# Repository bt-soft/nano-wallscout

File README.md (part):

# Pulzusindukciós (PI) betonvas-kereső – Arduino Nano + DD tekercs + MCP6004 + IRLZ44N + SSD1306

> [!NOTE]
> A projekt egy kézi impulzusindukciós (PI) elven működő - **mélységbecsléssel ellátott** - betonvas-kereső, amely két D alakú tekerccsel (DD elrendezés) működik. 
>
> Platform: **Arduino Nano (ATmega328P)**.

| Jellemző | Érték |
|---|---|
| Érzékelési mélység* | ≈5–6 cm, 8 cm becsült határeset (Ø8–12 mm betonvas, a tekercsek méretétől függően) |
| Kijelzés | SSD1306 OLED (oszlop, számérték, becsült mélység), hangjelzés |
| Tápellátás | 2S vagy 3S 18650 akkumulátor a Nano VIN bemenetén (lásd: Beüzemelés) |

 *Az értékek a tesztelési körülményektől, a tekercs geometriájától és a beállításoktól függnek.

## Az impulzusindukció működési elve
A kereső két tekercset használ: egy **adó (TX)** és egy **vevő (RX)** tekercset. A [tekercsek D alakúak](https://abl.gtu.edu.tr/dosya/102/~saksoy/Metal%20Detectors/1%20GENERAL%20OVERVIEW/2%20OPERATIONAL%20PRINCIPLES/2.1%20ANTENNAS.pdf), és az egyenes oldalaikkal részben egymásra vannak csúsztatva (DD elrendezés). Az alábbiak a működés fizikai alapjait foglalják össze.

### Az adóimpulzus és a mágneses tér
A Q2 kapcsolótranzisztor bekapcsolásakor az Ltx1 adótekercsre a tápfeszültség kerül, és az árama az induktivitás miatt lineárisan nő: `I ≈ U · t / L`. 12 V-nál, 60 µs-os impulzusnál és 1 mH-s tekercsnél ez elméletileg kb. 0,7 A; a tekercs ellenállása miatt a valós csúcsáram kb. 0,6 A. Az áram körül mágneses tér épül fel, amelynek energiája `E = ½ · L · I²`.

### Kikapcsolás és örvényáramok
A Q2 lezárásakor a mágneses tér gyorsan összeomlik. Ez a tekercsben nagy feszültségtüskét (flyback) okoz, amelyet a D2 és D3 diódák korlátoznak. A gyorsan változó tér a közelében lévő fémtárgyban **örvényáramot** indukál. Az örvényáram saját mágneses teret hoz létre, amely lecsengés közben visszahat a tekercsekre.

- Az örvényáram lecsengésének időállandója függ a tárgy méretétől, vezetőképességétől és mágneses permeabilitásától. A nagyobb, jobban vezető tárgynál a lecsengés hosszabb.
- A tárgy nélküli (levegős) esetben a tekercs saját tranziense gyorsan lecseng, ezért a rövid idő múlva mért jel gyakorlatilag nulla.
- A tárgy jelenléte így a lecsengés „farkában” mérhető többletjelként jelenik meg.

### A DD elrendezés és a közvetlen áthallás kioltása
Az [adó mágneses terének](doc/Fémkereső%20tekercsek%20betonvas%20kereséshez.png) közvetlenül az RX-be jutó része sokszorosan nagyobb lenne a fém jelénél. A két D alakú tekercs átfedésénél azonban a vevőtekercs két felét az adótér ellentétes irányban metszi, ezért a **kölcsönös induktivitás (M) a megfelelő átfedésnél nullára csökken**. A pontos átfedés a beállítási eljárás (DD beállító mód) feladata. A nullpont két oldalán M előjele ellentétes, ezért a beállításkor az előjelváltást kell keresni.

Ennek eredményeként fém jelenléte nélkül az RX tekercsre elsősorban a **maradék mágneses áthallás** és a **zaj** jut. Fém jelenlétében a benne indukálódó örvényáramok mágneses tere megváltoztatja a vevőtekercsben mérhető jelet. A megfelelően beállított DD-tekercspár esetén a fém nélküli alapjel alacsony, így a céltárgy által okozott jelváltozás jól érzékelhető.

A nagyobb tekercs megfelelő kialakítás esetén növelheti az érzékelési mélységet, de az elérhető eredmény a tekercsek geometriájától, induktivitásától, ellenállásától, a meghajtóáramtól és a vevő érzékenységétől is függ. A nagyobb tekercs térben kiterjedtebb érzékelési mezőt hozhat létre, ami ugyan növelheti a hatótávolságot, ugyanakkor ronthatja a céltárgy pontos helyének behatárolását.

A projektben alkalmazott, a kisebb 6 × 5 cm-es D alakú tekercspárral az érzékelési mélység körülbelül 5-6 cm. Ez az érték kísérletileg meghatározott (fémcsipeszt közelítve a tekercsek felé), illetve a mérési körülményektől és a céltárgy jellemzőitől függ.

### Jelfeldolgozás
Az Rx jele a mérendő tárgy hatására csak kis amplitúdójú, ezért az MCP6004 két, nem invertáló fokozata (kb. 11 × 11 = 121-szeres erősítés) erősíti, majd az U2D puffer az A0 bemenetre vezeti. A jelszint a Vmid (≈ 2,5 V) körül van, így a jel pozitív és negatív irányban is mérhető.

A mérés **mintavételes**, impulzusonként két ponton:
- **S1**: a kikapcsolás után 60 µs-mal. Ekkor a tárgy örvényárama még jelen van.
- **S2**: a kikapcsolás után 600 µs-mal. Ekkor az örvényáram lecsengett, így ez az alapvonal (offset, drift).

A **jel = S1 − S2**. A különbségképzés kiejti az egyenfeszültségű eltérést és a lassú driftet. 100 impulzus átlagolása a véletlenszerű zajt csökkenti (a zaj nagyjából az átlagolt minták számának négyzetgyökével csökken). A nullázáskor mért, fém nélküli értéket a firmware kivonja, így a megjelenített érték a tárgy hatását mutatja.

### Mélységbecslés
Kis, a tekercstől távoli tárgy esetén az örvényáram jele nagyjából a távolság harmadik hatványával csökken (dipól közelítés): `S ≈ K / d³`. A `K` értéket a kalibrálás határozza meg egy ismert (5 cm) távolságban, innen `d = ∛(K / S)`. Ez a modell a tárgy méretétől és anyagától függ, ezért a kapott érték becslés, nem pontos mérés.

### A fém típusa
Az impulzus utáni jel lecsengésének időbeli jellemzői elvileg információt hordozhatnak a céltárgy anyagáról. A jelenlegi, két időpontban történő mintavételezés és a hozzá tartozó jelfeldolgozás azonban nem biztosít megbízható anyagazonosítást, ezért ezt a funkciót eltávolítottam a firmware-ből.

## Működési ciklus

1. Az IRLZ44N (Q2) 60 µs-ra bekapcsol, a **Tx tekercs** (Ltx1) árama nő.
2. Kikapcsoláskor a flyback-tüskét a D2 (UF4007) és a D3 (ZPY36, 1 W) korlátozza; a névleges **lecsípési szint** nagyjából 37 V.
3. A tranziens lecsengését az Ltx1-gyel párhuzamos R15 + R16 ág (1 kΩ fix ellenállás + 4,7 kΩ-os trimmer) csillapítja. A fémben indukált örvényáram lassabban cseng le; ez a mérendő „farok”.
4. A **külön Rx tekercs** (Lrx1) az Ltx1-gyel DD elrendezésben (részben egymásra csúsztatva) helyezkedik el, így a közvetlen áthallás közel nulla, és az erősítőbe csak a fém által keltett jel jut.
5. A Nano 1 kHz-en ismétel, és impulzusonként két ponton mintavételez az ADC-vel: **S1** a kikapcsolás után 60 µs-mal, **S2** (alapvonal) 600 µs-mal.
6. Jel = S1 − S2, 100 impulzusra átlagolva (kb. 7 Hz kijelzőfrissítés). Ez kiejti az offsetet és a lassú driftet.
7. Indításkor automatikus nullázás történik (a kereső legyen levegőben). Az alapvonal lassan követi a driftet. Egy találat előjelét a firmware megtartja; az ellenkező előjelű kilengést csak 1 másodpercnyi küszöb alatti jel után kezdi új találatként kezelni. Ha a jel kb. 3 másodpercnél tovább állandó marad (pl. nullpont-eltolódás), a firmware lassan újranulláz; egy mozdulatlanul tartott fém így néhány másodperc után elhalkul.
8. A kijelző oszlopot, számértéket és (kalibrálás után) becsült mélységet mutat. A hangjelzés magassága a jellel nő.

### Szoftverműködés – bevezető

A firmware az időkritikus részeken az **AVR hardverregisztereket közvetlenül kezeli** (`PORTD`, `PIND`, `DDRD`, `TCNT1`, `TCCR1/2`, `ADCSRA`, `ADMUX`, `PCMSK2` stb.) az Arduino `digitalWrite`/`analogRead`-jellegű, lassabb és nagyobb kódú burkolófüggvényei helyett. Ez minimalizálja a kód méretét (a program a Nano 30 KB-os flash-ébe fér), és tartja a futási sebességet: a 60 µs-os adóimpulzus, a kikapcsolás utáni S1/S2 mintavétel (0,5 µs-os Timer1-időalap, gyors, 1 MHz-es ADC-órajel) és a hangjelző (Timer2 hardveres kimenet, CPU-terhelés nélkül) így determinisztikus időzítéssel fut.

### Alvó mód (energiatakarékosság)

Ha **5 percig** nincs aktivitás, a műszer a lehető legkisebb fogyasztású **Power-down** módba kapcsol. Aktivitásnak számít: gombnyomás, aktív találat, vagy a nullázás utáni zajküszöböt meghaladó jelváltozás (a zaj nem tartja ébren). Az időkorlát a `config.h` `IDLE_SLEEP_MS` értéke.

Alvás előtt a firmware kikapcsolja a hangjelzőt, az adókaput (az adó nem kap impulzust), az OLED-et (power save, I²C leállítva), az ADC-t és az analóg bemenetek digitális pufferét, a Brown-out detektort és a watchdogot, valamint az összes perifériát (`power_all_disable`).

Ébresztés: a **kalibráló vagy a nullázó gomb** megnyomásával (pin change megszakítás), illetve a tápfeszültség újrakapcsolásával. Ébredés után a készülék újrainicializálódik, megvárja a gomb felengedését (az ébresztő nyomás nem lesz parancs), majd az indításhoz hasonlóan újranulláz – ilyenkor a kereső legyen levegőben.

Megjegyzés: a vevő (erősítő) tápját a firmware nem tudja kapcsolni, mert nincs rá vezérlőláb; az adó viszont impulzus nélkül áramot nem vesz fel. A legkisebb alvóáramhoz a vevő és a kijelző tápja hardveresen is leválasztható egy későbbi fejlesztésben.

### Gombok

Mindkét gomb a D-lábat földre húzza (belső felhúzással). A gombokat a mérés közben is figyeli a firmware, de a művelet a következő kijelzőfrissítéskor (kb. 0,1–0,2 s) hajtódik végre.

**Arduino D5 – NULLÁZÁS / beállító mód**

| Művelet | Normál (kereső) módban | DD beállító módban |
|---|---|---|
| Rövid nyomás (< 1 s), **felengedéskor** lép életbe | Újranullázás: a kijelzőn `Nullazas - legben!`, kb. 15 mérésen át (≈ 2 s) átlagolja a nullpontot és a zajszintet (a küszöb a zajhoz igazodik). Közben a kereső legyen levegőben, és ne legyen jelzés/csipogás. | Kilép a beállító módból, és újranulláz. |
| Hosszú nyomás (≥ 1 s), **még nyomva tartva** lép életbe | Belép a DD beállító módba (a `min` törlődik). | Nincs külön szerepe: a felengedéskor ugyanúgy kilép és újranulláz, mint a rövid nyomás. |

A mód váltását rövid (150 ms-os), 3 kHz-es csipogás jelzi. A hosszú nyomás után a gomb felengedése már nem indít újabb műveletet.

**Arduino D4 – KALIBRÁLÁS / KÖZÉPKERESŐ / `min` törlése**

Normál kereső módban a D4 rövid megnyomásai a következő nézetek között léptetnek: normál keresés → élő `CENTER SCAN` → `Jel-Ido` grafikon → normál keresés. A grafikon folyamatosan gyűjti a méréseket: az amplitúdó jobbról érkezik, a korábbi minták balra gördülnek, így a jel erősségének időbeli alakulása követhető. A grafikon a nullázott jel abszolút értékét mutatja; a szaggatott vízszintes vonal az adaptív küszöb. A hosszú nyomás a távolságtanító képernyőt nyitja meg (lásd lent). DD beállító módban a D4 megnyomása törli a `min` értéket (eddigi legkisebb abszolút áthallás), és újra a következő mérésből indul.

Középkereső módban a kijelző az előjeles, nullázott jelet, annak rövid gördülő grafikonját, a zajküszöböt, az első és a visszapásztázás során mért csúcsot mutatja. A firmware legalább két küszöb feletti mintával jelöltet keres, több csökkenő minta alapján becsül csúcsot, majd visszapásztázás után a két csúcserősséget hasonlítja össze. A `CSUCS MEGEROSITVE` csak ezt a jelerősség-egyezést jelenti: a mintasorszám nem pozíció, így a mód nem mér és nem jelöl ki pontos fizikai középvonalat. A visszapásztázás irányát nem nevezi meg.

A mód bekapcsolásakor a mérő legyen levegőben és fémtől távol. Ha a `ZAJOS MERES` felirat látszik, válassz kevésbé zajos helyet és nullázz újra a D5 rövid megnyomásával. Középkereső módban a driftkövetés és az automatikus újranullázás szünetel, így a hosszan a tekercs alatt tartott tárgyat nem nyomja el a háttérkövetés. A visszalépéshez nyomd meg röviden újra a D4-et.

Normál módban:

1. Tartsd lenyomva a D4-et **1 másodpercig**: megnyílik a `TANITAS 5cm` képernyő, amely folyamatosan mutatja a vett jelet, egy oszlopot és (érvényes kalibráció esetén) a becsült távolságot. A képernyőn a driftkövetés szünetel.
2. Tarts egy vasat (a használt vastípust) pontosan **5 cm**-re a tekercstől, és nyomd meg röviden a D4-et. Ha a jel a küszöb fölött van, a firmware eltárolja a `K = jel · 5³` értéket (az `S ≈ K/d³` modellre), az **EEPROM**-ba menti (kikapcsolás után is megmarad), 3 kHz-es csipogás hallatszik, és 1,5 s-ig `Rogzitve: 5 cm` látszik. A képernyő nyitva marad, így a rögzítés tetszőleges számú alkalommal megismételhető, és a becsült távolság azonnal ellenőrizhető.
3. Ha nincs elég jel, a mentés **nem** történik meg: `Nincs jel!` (vagy túlvezérlésnél `Tulvezerles!`) jelenik meg. Hozd közelebb a vasat, és próbáld újra.
4. Kilépés: a D5 rövid megnyomása (újranullázás nélkül) vagy a D4 ismételt hosszú nyomása.
5. Nullázás közben (`Nullazas - legben!`) a tanítóképernyő nem nyitható meg.

Kalibrálás nélkül a kijelzőn `nincs kal.` látszik, és mélység nem jelenik meg.

Mélység: d = ∛(K/S). Ez a mélység becslése, nem pontos mérés.

### Középkereső paraméterei és ellenőrzése

Az induló értékek a `include/config.h` fájlban vannak; prototípuson, ismert geometriájú célokkal kell őket hangolni.

| Paraméter | Kezdőérték | Szerep |
|---|---:|---|
| `CENTER_CONFIRM_SAMPLES` | 2 | Egymást követő minták a jelölt, illetve a visszatérő emelkedés elfogadásához |
| `CENTER_FALLING_SAMPLES` | 3 | Egymást követő csökkenő minták a lokális csúcs felismeréséhez |
| `CENTER_STAGE_TIMEOUT_MS` | 20000 ms | Csúcskövetési vagy visszapásztázási szakasz maximális ideje; lejáratkor új keresés indul |
| `CENTER_RELEASE_FRACTION` | 0,70 | A küszöb alá eső jel elvetési aránya (hiszterézis) |
| `CENTER_PEAK_HYSTERESIS_FRACTION` | 0,20 | Minimális csúcstól való esés az adaptív zajküszöbhöz képest |
| `CENTER_MIN_RETURN_DROP_FRACTION` | 0,30 | A visszapásztázás előtti völgy minimuma az első csúcshoz viszonyítva |
| `CENTER_RETURN_TOLERANCE_FRACTION` | 0,35 | A két irányban mért csúcserősség megengedett relatív eltérése |
| `CENTER_RETURN_MIN_TOLERANCE` | 2,0 | A csúcsegyezés minimális tűrése a zajküszöb többszörösében |
| `CENTER_NOISY_THRESHOLD` | 8,0 | Ezen adaptív küszöb felett zajos mérés figyelmeztetés |
| `SIGNAL_TIME_GRAPH_SIZE` | 32 | A Jel-Ido grafikon rögzített mintaszáma |

Kalibráláskor a kereső legyen levegőben, fémtől távol és a végleges mechanikai elrendezésben. Fém nélküli stabil, majd zajos környezetben ellenőrizd a soros `noise_th` értéket; a `CENTER_NOISY_THRESHOLD`-öt és a többi értéket csak ilyen mérések után módosítsd. Ezután tesztelj több ismert átmérőjű és mélységű betonvassal, mindkét pásztázási irányban és különböző kézi sebességgel. Jegyezd fel a megismételt csúcsok eltérését, a téves találatokat és a fel nem ismert célokat.

Elfogadási próbák: fém nélküli stabil/zajos mérés; egyetlen széles csúcs oda-vissza pásztázása; egyetlen rövid küszöb feletti tüske; változó és többcsúcsú jel; két közeli fémtárgy; lassú nullpontvándorlás; gyenge vagy hatótávon túli cél; hosszan egy helyben tartott cél; nullázás vagy DD-mód váltása középkeresés közben. A visszatérő csúcs nem erősíthető meg egyetlen tüskéből: a logikának a völgy után két egymást követő emelkedő mintát, majd több csökkenő mintát és a csúcserősségek egyezését igényli. Ezek szoftveres feltételek, nem garantálják a betonvas tényleges geometriai középvonalát.

### Soros monitor (115200 baud)

> [!WARNING]
> Ha a fordítás során a [__DEBUG__](https://github.com/bt-soft/nano-wallscout/blob/main/src/main.cpp#L12) makró definiálva van, az AVR debugger 
> aktiválódik. Ha emellett a [__DEBUG_SERIAL_LOGGING__](https://github.com/bt-soft/nano-wallscout/blob/main/src/main.cpp#L13) makró is definiálva 
> van, az Arduino soros portján keresztüli naplózás aktiválódik, az AVR debugger viszont nem. 
> **A két funkció egyidejűleg nem használható.**

Minden mérés (kb. 0,1–0,2 s) után egy sor jelenik meg, pl. `run diff=3.20 raw_diff=3.20 s1=512 s2=510 idle=511 zero=0.40 sig=2.80 vbat=11.8`. Az elején `run` (kereső), `center` (középkereső) vagy `setup ch=A0` (DD beállító mód) áll. Középkereső módban a `center_sig`, `noise_th`, `center_state`, `peak`, `return_peak`, `peak_sample` és `return_sample` mezők is megjelennek. A mintasorszám diagnosztikai adat, nem fizikai távolság. Az értékek ADC-egységben (0–1023) vannak, 100 impulzusra átlagolva.

| Mező | Jelentés |
|---|---|
| `s1` | Az első mintavétel átlaga az A0 bemeneten: a Tx kikapcsolása után 60 µs-mal (`T_SAMPLE1`). Ebben van a fém örvényáramának lecsengő jele. Nyugalmi értéke ≈ 512 (Vmid). 950 fölött vagy 70 alatt az erősítő telít, ekkor `TULVEZERLES`. |
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
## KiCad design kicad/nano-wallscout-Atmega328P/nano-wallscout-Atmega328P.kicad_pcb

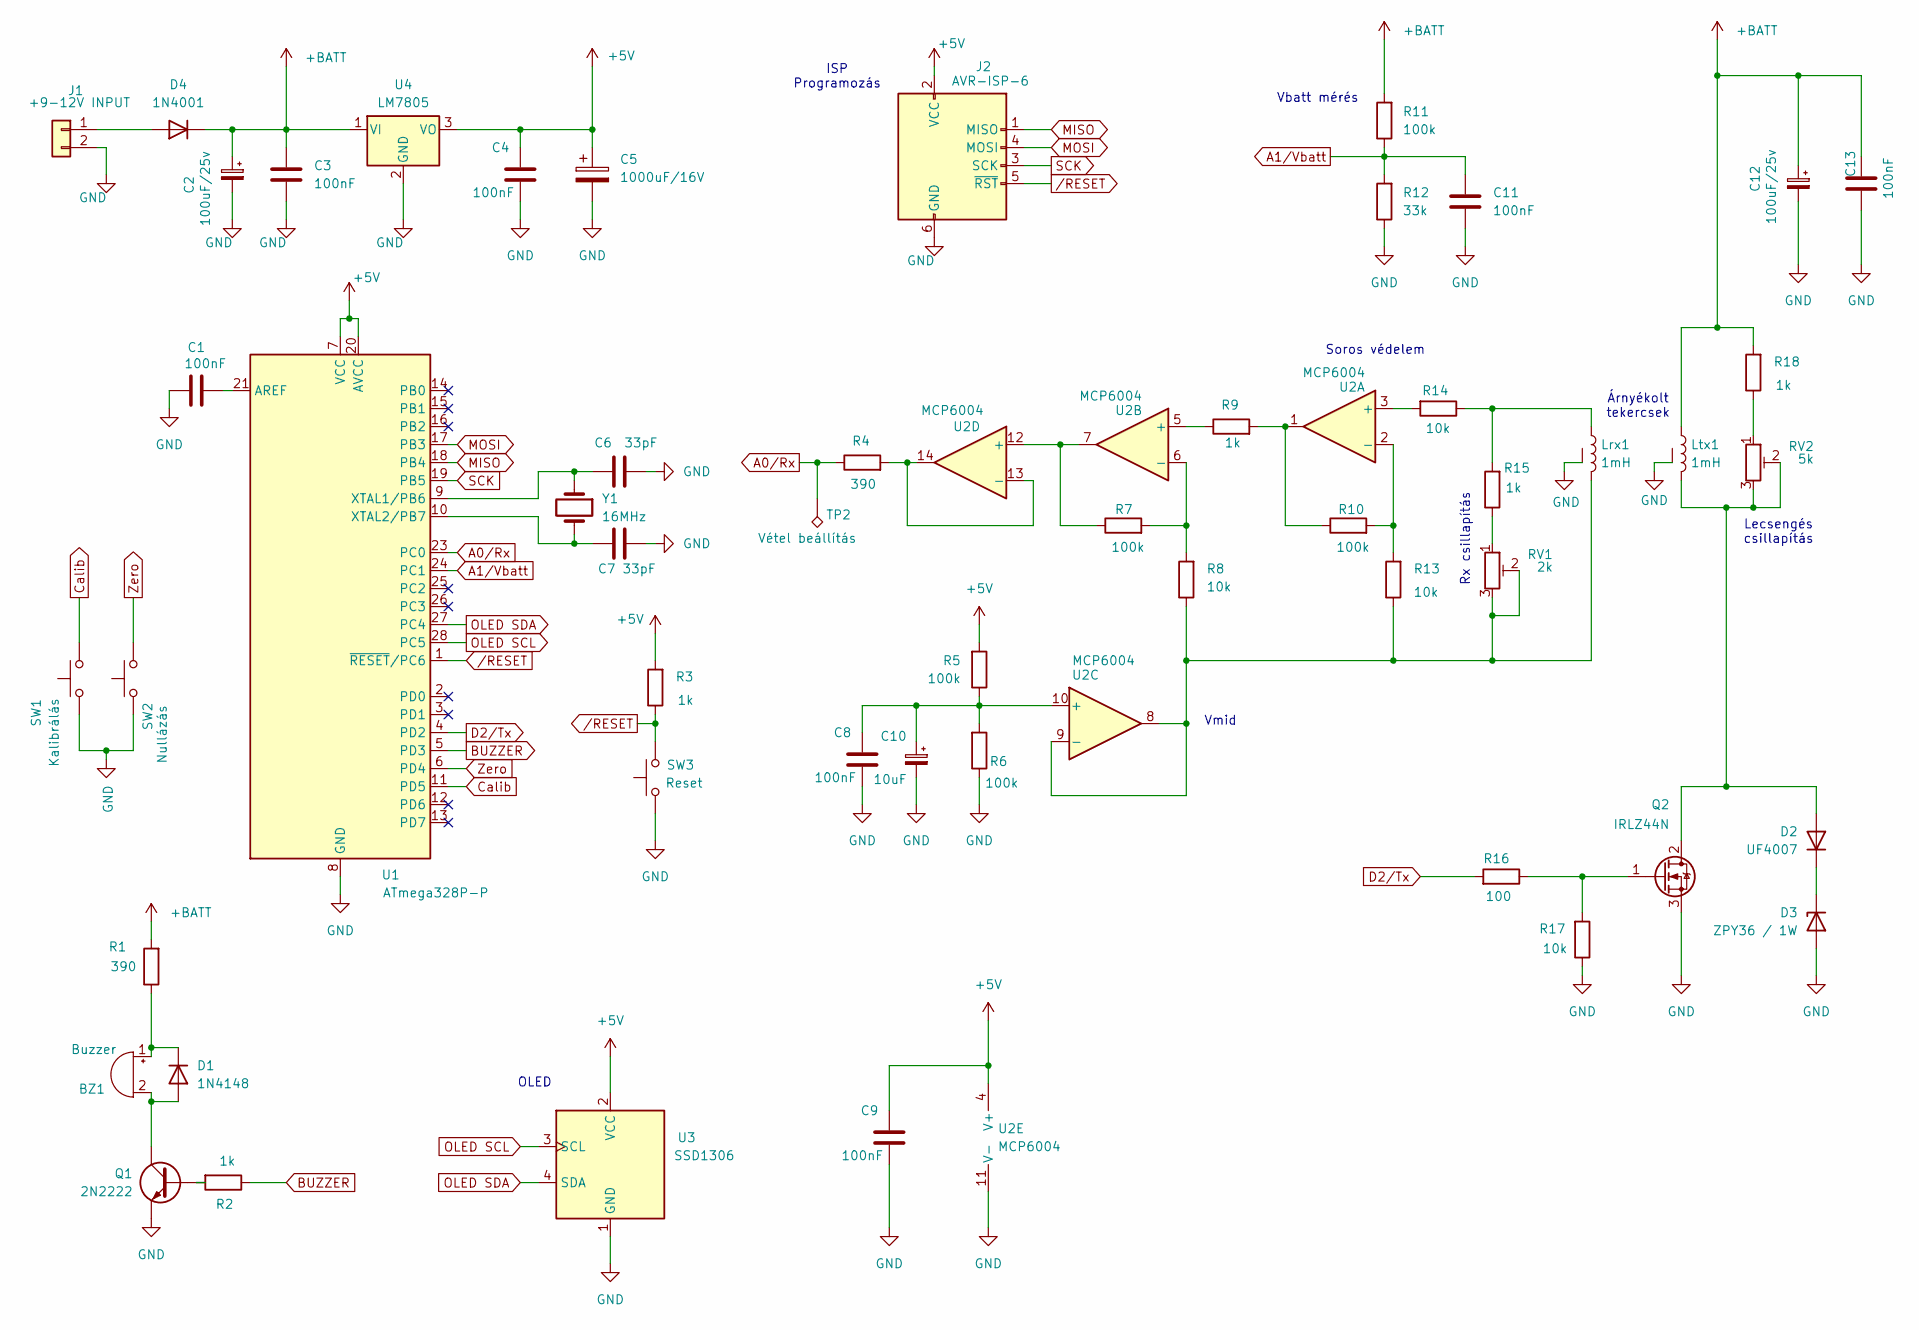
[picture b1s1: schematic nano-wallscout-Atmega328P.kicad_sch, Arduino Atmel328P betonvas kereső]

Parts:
BZ1: Buzzer; Buzzer_TDK_PS1240P02BT_D12.2mm_H6.5mm
C1, C3, C4, C8, C9, C11, C13: 100nF; C_Rect_L7.2mm_W2.5mm_P5.00mm
C2, C12: 100uF/25v; CP_Radial_D6.3mm_P2.50mm
C5: 1000uF/16V; CP_Radial_D10.0mm_P5.00mm
C6, C7: 33pF; C_Disc_D3.0mm_W2.0mm_P2.50mm
C10: 10uF; CP_Radial_D6.3mm_P2.50mm
D1: 1N4148; D_DO-35_SOD27_P10.16mm_Horizontal
D2: UF4007; D_DO-35_SOD27_P10.16mm_Horizontal
D3: ZPY36 / 1W; D_DO-35_SOD27_P10.16mm_Horizontal
D4: 1N4001; D_DO-41_SOD81_P10.16mm_Horizontal
J1: +9-12V INPUT; TerminalBlock_Phoenix_PT-1,5-2-5.0-H_1x02_P5.00mm_Horizontal
J2: AVR-ISP-6; PinHeader_2x03_P2.54mm_Vertical
Lrx1: 1mH; TerminalBlock_Phoenix_PT-1,5-3-3.5-H_1x03_P3.50mm_Horizontal
Ltx1: 1mH; TerminalBlock_Phoenix_PT-1,5-3-3.5-H_1x03_P3.50mm_Horizontal
Q1: 2N2222; TO-92_Inline_Wide
Q2: IRLZ44N; TO-220-3_Vertical
R1, R4: 390; R_Axial_DIN0207_L6.3mm_D2.5mm_P10.16mm_Horizontal
R2, R3, R9, R15, R18: 1k; R_Axial_DIN0207_L6.3mm_D2.5mm_P10.16mm_Horizontal
R5, R6, R7, R10, R11: 100k; R_Axial_DIN0207_L6.3mm_D2.5mm_P10.16mm_Horizontal
R8, R13, R14, R17: 10k; R_Axial_DIN0207_L6.3mm_D2.5mm_P10.16mm_Horizontal
R12: 33k; R_Axial_DIN0207_L6.3mm_D2.5mm_P10.16mm_Horizontal
R16: 100; R_Axial_DIN0207_L6.3mm_D2.5mm_P10.16mm_Horizontal
RV1: 2k; Potentiometer_Bourns_3266Y_Vertical
RV2: 5k; Potentiometer_Bourns_3266Y_Vertical
SW1: Kalibrálás; SW_PUSH_6mm_H8mm
SW2: Nullázás; SW_PUSH_6mm_H8mm
SW3: Reset; SW_PUSH_6mm_H8mm
TP2: Vétel beállítás; TestPoint_Loop_D2.50mm_Drill1.0mm
U1: ATmega328P-P; DIP-28_W7.62mm
U2: MCP6004; DIP-14_W7.62mm_LongPads
U3: SSD1306; PinHeader_1x04_P2.54mm_Vertical
U4: LM7805; TO-220-3_Vertical
Y1: 16MHz; Crystal_HC49-4H_Vertical

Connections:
+5V: C4.2, C5.1, C9.2, J2.2 (VCC), R3.2, R5.2, U1.7 (VCC), U1.20 (AVCC), U2.4 (V+), U3.2 (VCC), U4.3 (VO)
+BATT: C2.1, C3.1, C12.1, C13.2, D4.1 (K), Ltx1.1, R1.2, R11.2, R18.2, U4.1 (VI)
A0/Rx: R4.1, TP2.1 (1_1), U1.23 (PC0)
A1/Vbatt: C11.1, R11.1, R12.2, U1.24 (PC1)
BUZZER: R2.1, U1.5 (PD3)
Calib: SW1.2, U1.11 (PD5)
D2/Tx: R16.2, U1.4 (PD2)
GND: C1.2, C2.2, C3.2, C4.1, C5.2, C6.1, C7.1, C8.1, C9.1, C10.2, C11.2, C12.2, C13.1, D3.2 (A), J1.2, J2.6 (GND), Lrx1.3 (SHIELD), Ltx1.3 (SHIELD), Q1.3 (E), Q2.3 (S), R6.1, R12.1, R17.1, SW1.1, SW2.1, SW3.1, U1.8 (GND), U1.22 (GND), U2.11 (V-), U3.1 (GND), U4.2 (GND)
MISO: J2.1 (MISO), U1.18 (PB4)
MOSI: J2.4 (MOSI), U1.17 (PB3)
unnamed: BZ1.1 (+), D1.1 (K), R1.1
unnamed: BZ1.2 (-), D1.2 (A), Q1.1 (C)
unnamed: D2.2 (A), Ltx1.2, Q2.2 (D), RV2.2, RV2.3
unnamed: D2.1 (K), D3.1 (K)
unnamed: D4.2 (A), J1.1
unnamed: Lrx1.1, R14.1, R15.2
unnamed: Q1.2 (B), R2.2
unnamed: Q2.1 (G), R16.1, R17.2
unnamed: R9.2, R10.1, U2.1
unnamed: R15.1, RV1.1
unnamed: R18.1, RV2.1
unnamed: C1.1, U1.21 (AREF)
unnamed: C6.2, U1.9 (XTAL1/PB6), Y1.1
unnamed: C7.2, U1.10 (XTAL2/PB7), Y1.2
unnamed: R14.2, U2.3 (+)
unnamed: R10.2, R13.2, U2.2 (-)
unnamed: R9.1, U2.5 (+)
unnamed: R7.2, R8.2, U2.6 (-)
unnamed: C8.2, C10.1, R5.1, R6.2, U2.10 (+)
unnamed: Lrx1.2, R8.1, R13.1, RV1.2, RV1.3, U2.8, U2.9 (-)
unnamed: R7.1, U2.7, U2.12 (+)
unnamed: R4.2, U2.13 (-), U2.14
OLED SCL: U1.28 (PC5), U3.3 (SCL)
OLED SDA: U1.27 (PC4), U3.4 (SDA)
SCK: J2.3 (SCK), U1.19 (PB5)
Zero: SW2.2, U1.6 (PD4)
/RESET: J2.5 (~RST), R3.1, SW3.2, U1.1 (~RESET/PC6)

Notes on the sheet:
Lecsengés csillapítás
Vmid
Árnyékolt tekercsek
Rx csillapítás
Vbatt mérés
ISP Programozás
OLED
Soros védelem

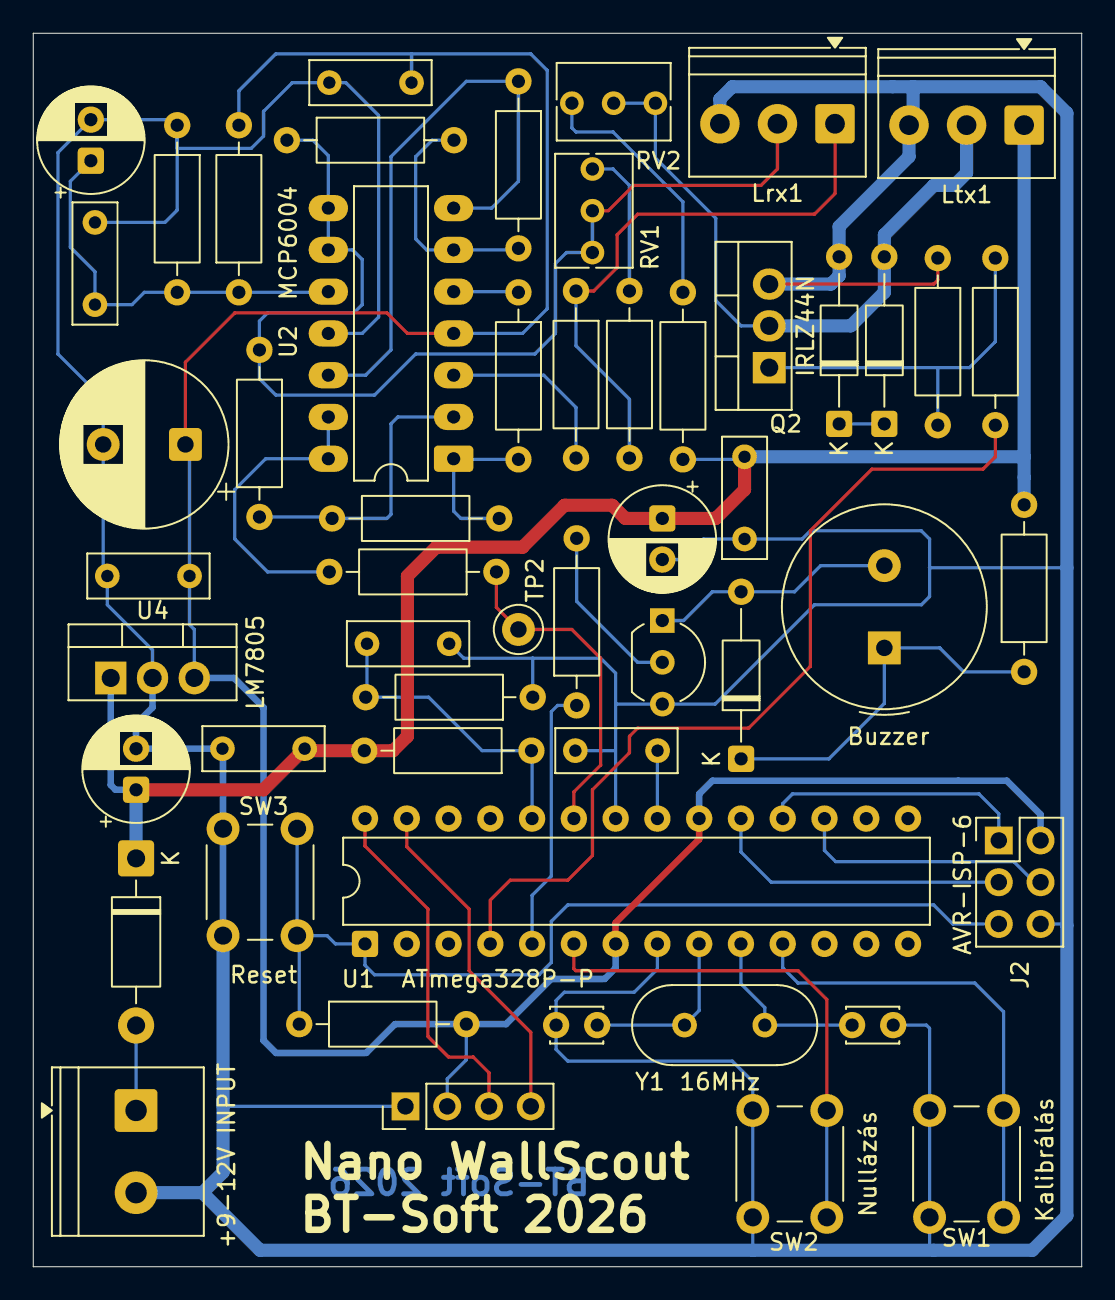
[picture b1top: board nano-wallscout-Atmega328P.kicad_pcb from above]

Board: 2 copper layers, 63.8 x 75.0 mm, 53 parts (0 on the bottom side), 37 nets.

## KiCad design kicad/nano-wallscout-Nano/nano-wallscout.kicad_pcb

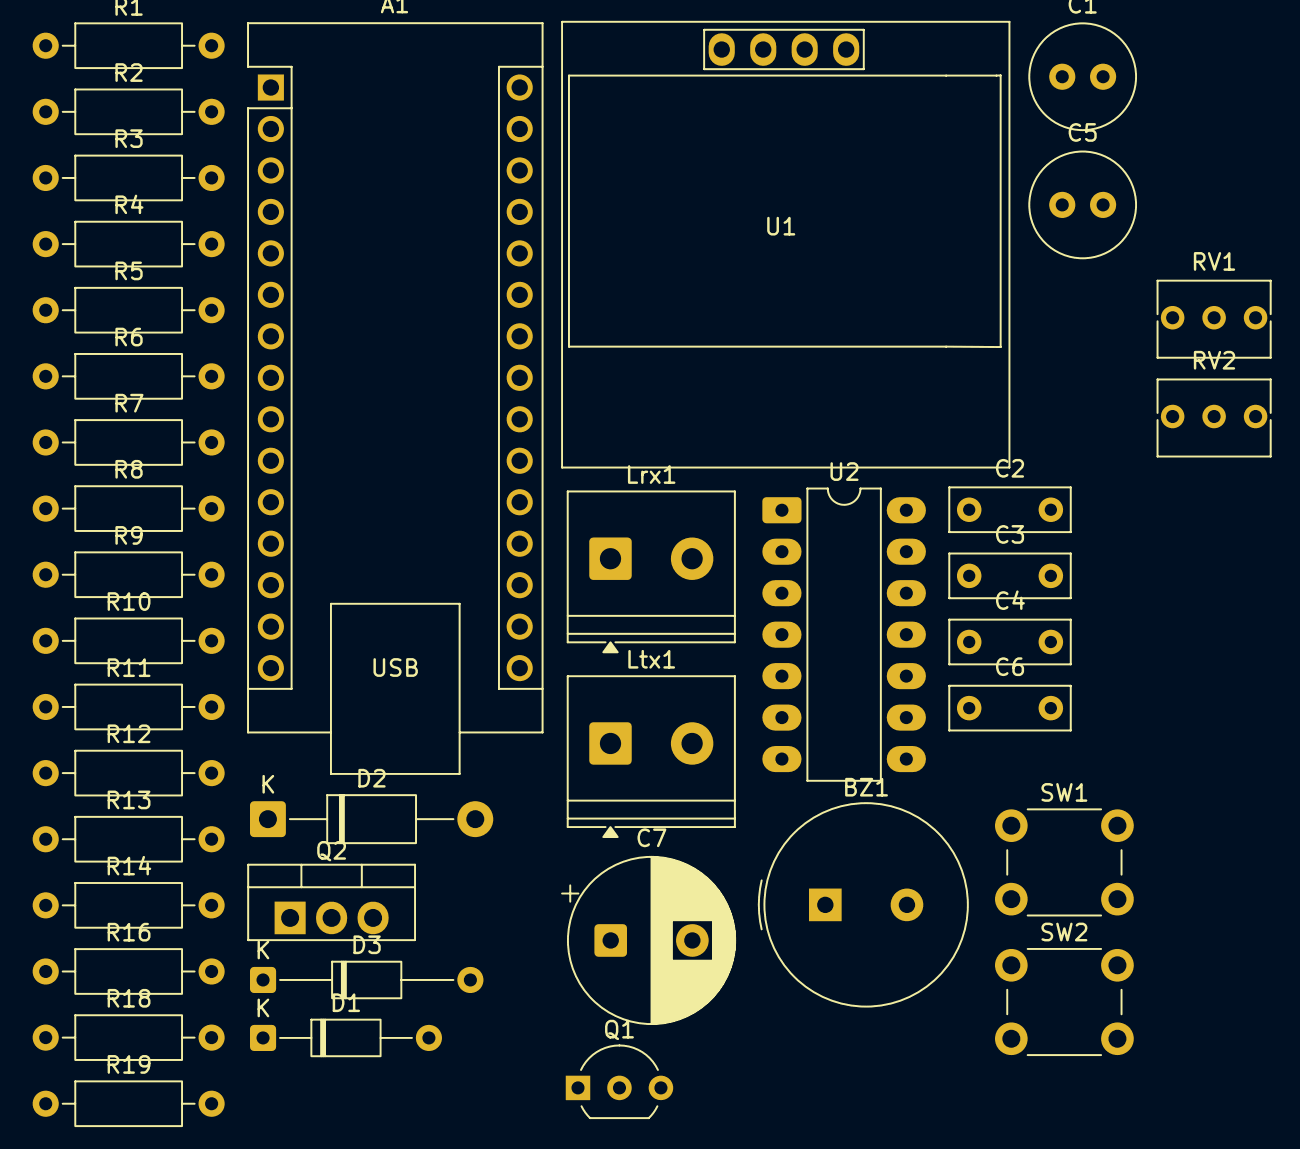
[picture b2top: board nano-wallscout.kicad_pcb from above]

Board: 2 copper layers, 39 parts (0 on the bottom side), 29 nets, no tracks yet.

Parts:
A1: Arduino_Nano_v2.x; Arduino_Nano
BZ1: Buzzer; Buzzer_TDK_PS1240P02BT_D12.2mm_H6.5mm
C1: 100uF/25v; C_Radial_D6.3mm_H11.0mm_P2.50mm
C2, C3, C4, C6: 100nF; C_Rect_L7.2mm_W2.5mm_P5.00mm
C5: 10uF; C_Radial_D6.3mm_H11.0mm_P2.50mm
C7: 1000uF/16V; CP_Radial_D10.0mm_P5.00mm
D1: 1N4148; D_DO-35_SOD27_P10.16mm_Horizontal
D2: UF4007; D_DO-41_SOD81_P12.70mm_Horizontal
D3: ZPY36 / 1W; D_DO-35_SOD27_P12.70mm_Horizontal
Lrx1: 1mH; TerminalBlock_Phoenix_PT-1,5-2-5.0-H_1x02_P5.00mm_Horizontal
Ltx1: 1mH; TerminalBlock_Phoenix_PT-1,5-2-5.0-H_1x02_P5.00mm_Horizontal
Q1: 2N2222; TO-92_Inline_Wide
Q2: IRLZ44N; TO-220-3_Vertical
R1: 150; R_Axial_DIN0207_L6.3mm_D2.5mm_P10.16mm_Horizontal
R2, R10, R14, R16: 1k; R_Axial_DIN0207_L6.3mm_D2.5mm_P10.16mm_Horizontal
R3, R6, R7, R8, R11: 100k; R_Axial_DIN0207_L6.3mm_D2.5mm_P10.16mm_Horizontal
R4: 33k; R_Axial_DIN0207_L6.3mm_D2.5mm_P10.16mm_Horizontal
R5: 390; R_Axial_DIN0207_L6.3mm_D2.5mm_P10.16mm_Horizontal
R9, R12, R13, R19: 10k; R_Axial_DIN0207_L6.3mm_D2.5mm_P10.16mm_Horizontal
R18: 100; R_Axial_DIN0207_L6.3mm_D2.5mm_P10.16mm_Horizontal
RV1: 2k; Potentiometer_Bourns_3266Y_Vertical
RV2: 5k; Potentiometer_Bourns_3266Y_Vertical
SW1: Kalibrálás; SW_PUSH_6mm_H8mm
SW2: Nullázás; SW_PUSH_6mm_H8mm
U1: SSD1306; 128x64OLED
U2: MCP6004; DIP-14_W7.62mm_LongPads

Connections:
+5V: A1.27 (+5V), C6.2, C7.1, R1.2, R6.2, U1.2 (VCC), U2.4 (V+)
+BATT: A1.30 (VIN), C1.1, C2.2, Ltx1.1, R3.2, R16.2
GND: A1.4 (GND), A1.29 (GND), C1.2, C2.1, C3.1, C4.2, C5.2, C6.1, C7.2, D3.2 (A), Q1.3 (E), Q2.3 (S), R4.1, R7.1, R19.1, SW1.1, SW2.1, U1.1 (GND), U2.11 (V-)
unnamed: A1.19 (A0), R5.1
unnamed: A1.20 (A1), C4.1, R3.1, R4.2
unnamed: A1.23 (A4), U1.4 (SDA)
unnamed: A1.24 (A5), U1.3 (SCL)
unnamed: A1.5 (D2), R18.2
unnamed: A1.7 (D4), SW1.2
unnamed: A1.8 (D5), SW2.2
unnamed: A1.14 (D11), R2.1
unnamed: BZ1.1 (+), D1.1 (K), R1.1
unnamed: BZ1.2 (-), D1.2 (A), Q1.1 (C)
unnamed: D2.2 (A), Ltx1.2, Q2.2 (D), RV2.2, RV2.3
unnamed: D2.1 (K), D3.1 (K)
unnamed: Lrx1.1, R13.1, R14.2
unnamed: Q1.2 (B), R2.2
unnamed: Q2.1 (G), R18.1, R19.2
unnamed: R10.2, R11.1, U2.1
unnamed: R14.1, RV1.1
unnamed: R16.1, RV2.1
unnamed: R13.2, U2.3 (+)
unnamed: R11.2, R12.2, U2.2 (-)
unnamed: R10.1, U2.5 (+)
unnamed: R8.2, R9.2, U2.6 (-)
unnamed: C3.2, C5.1, R6.1, R7.2, U2.10 (+)
unnamed: Lrx1.2, R9.1, R12.1, RV1.2, RV1.3, U2.8, U2.9 (-)
unnamed: R8.1, U2.7, U2.12 (+)
unnamed: R5.2, U2.13 (-), U2.14

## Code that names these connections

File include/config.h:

/**
 * @file A betonvas-kereső közös hardveres és mérési beállításai.
 */
#pragma once

#include <Arduino.h>

/**
 * @brief Engedélyezi a soros naplózást és a hibakeresést.
 *
 *  A Soros naplózás és az AVR8-stub hibakeresés együtt nem használható!!
 *  https://docs.platformio.org/en/stable/plus/debug-tools/avr-stub.html
 */
// #define __DEBUG__

/**
 * @brief Középkereső képernyő fordítása
 *
 * Ezt kikapcsolva a kód nem kerül a firmware-be
 */
// #define ENABLE_CENTER_FINDER_SCREEN

/**
 * @brief Az Arduino Nano lábkiosztása a kapcsolási rajz szerint.
 *
 * D4: kalibrálógomb;
 * D5: nullázó- és DD-beállítógomb;
 * D2: Q2 FET kapuja.
 * D3: hangjelző;
 * A0: mérőjel;
 * A1: akkumulátorfeszültség-osztó.
 * A4 és A5: OLED I²C-kapcsolat.
 */
#define GATE_BIT PD2     // Q2 FET Gate lábának bitje a PORTD regiszterben
#define PIN_BUZZER PD3   // Hangjelző lábának bitje a PORTD regiszterben
#define PIN_BTN_CAL PD4  // Kalibrálógomb lába
#define PIN_BTN_ZERO PD5 // Nullázó- és DD-beállítógomb lába

/** @brief A Q2 FET bekapcsolási ideje mikroszekundumban. */
static const uint16_t T_ON = 60;

/** @brief Az impulzusok periódusideje mikroszekundumban. */
static const uint16_t T_PERIOD = 1000;

/** @brief Az első minta időpontja a Q2 FET kikapcsolása után, mikroszekundumban. */
static const uint16_t T_SAMPLE1 = 60;

/** @brief A referencia-minta időpontja a Q2 FET kikapcsolása után,
 * mikroszekundumban. */
static const uint16_t T_SAMPLE2 = 600;

/** @brief A DD-csatolás mintavételi időpontja a Q2 bekapcsolása után,  mikroszekundumban. */
static const uint16_t T_COUPLE = 40;

/** @brief Az egy méréshez átlagolt impulzusok száma. */
static const uint16_t N_PULSES = 100;

/** @brief A Timer1 időzítőütéseinek száma mikroszekundumonként. */
static const uint16_t TICKS_PER_US = 2;

/** @brief A találat érzékelési küszöbe ADC-egységben. */
static const float DETECT_TH = 1.3f;

/** @brief A találat kikapcsolási küszöbe a bekapcsolási küszöb (`runTh`) arányában; ez adja a hiszterézist. */
static const float DETECT_RELEASE_FRACTION = 0.6f;

/** @brief A nullázáskor mért zaj szórásának szorzója az adaptív küszöbhöz (`runTh`). */
static const float NOISE_TH_FACTOR = 5.0f;

/** @brief A kalibrálás nélküli teljes kijelzőskálához tartozó jel. */
static const float FULL_SCALE = 60.0f;

/** @brief A DD-beállítás logaritmikus skálájának teljes értéke. */
static const float SETUP_FULL = 500.0f;

/** @brief A kalibráláshoz használt ismert mélység centiméterben. */
static const float CAL_DEPTH_CM = 5.0f;

/** @brief Az akkumulátor feszültségosztójának aránya. (100k + 33k) / 33k */
static const float BATT_DIV = (100.0f + 33.0f) / 33.0f;

/** @brief Az indulási nullázáshoz szükséges mérési ciklusok száma. */
static const uint16_t ZERO_UPDATES = 15;

/** @brief A hosszú gombnyomás küszöbideje milliszekundumban. */
static const uint32_t LONG_PRESS_MS = 1000;

/** @brief A nullpont lassú követésének súlya küszöb alatti jelnél. */
static const float DRIFT_FOLLOW = 0.02f;

/** @brief Ennyi egymást követő küszöb feletti mérés kell a jelölt megerősítéséhez. */
static const uint8_t CENTER_CONFIRM_SAMPLES = 2;

/** @brief Ennyi csökkenő mérés kell egy lehetséges csúcshoz. */
static const uint8_t CENTER_FALLING_SAMPLES = 3;

/** @brief Időtúllépés a csúcskövetési és a visszapásztázási szakaszra milliszekundumban. */
static const uint32_t CENTER_STAGE_TIMEOUT_MS = 20000;

/** @brief A keresési küszöb alatti visszaesés aránya a jelölt törléséhez. */
static const float CENTER_RELEASE_FRACTION = 0.70f;

/** @brief A csúcstól elvárt minimális visszaesés aránya a zajküszöbhöz képest. */
static const float CENTER_PEAK_HYSTERESIS_FRACTION = 0.20f;

/** @brief A visszapásztázás előtt szükséges minimális jelcsökkenés az első csúcshoz képest. */
static const float CENTER_MIN_RETURN_DROP_FRACTION = 0.30f;

/** @brief A két pásztázás csúcserőssége közötti megengedett relatív eltérés. */
static const float CENTER_RETURN_TOLERANCE_FRACTION = 0.35f;

/** @brief A visszatérő csúcs minimális abszolút eltéréstűrése a becsült zajküszöb többszörösében. */
static const float CENTER_RETURN_MIN_TOLERANCE = 2.0f;

/** @brief E feletti adaptív küszöbnél a középkereső zajos mérést jelez. Hangolása valós mérést igényel. */
static const float CENTER_NOISY_THRESHOLD = 8.0f;

/** @brief A Jel-Ido nézet gördülő jelgrafikonjának rögzített mintaszáma. */
static const uint8_t SIGNAL_TIME_GRAPH_SIZE = 32;

/** @brief Az exponenciális simítás súlya normál üzemmódban. A kisebb érték lassabban követi a jelváltozásokat. */
static const float SMOOTH_RUN = 0.5f;

/** @brief Az exponenciális simítás súlya DD-beállító módban. A kisebb érték lassabban követi a jelváltozásokat. */
static const float SMOOTH_SETUP = 0.1f;

/** @brief Ennél nagyobb ugrásnál a simítás új értékről indul. */
static const float SMOOTH_JUMP = 60.0f;

/** @brief A túlvezérlés felső ADC-küszöbe. */
static const float OVERLOAD_HIGH = 950.0f;

/** @brief A túlvezérlés alsó ADC-küszöbe. */
static const float OVERLOAD_LOW = 70.0f;

/** @brief A DC-hiba felső ADC-küszöbe. */
static const uint16_t IDLE_HIGH = 900;

/** @brief A DC-hiba alsó ADC-küszöbe. */
static const uint16_t IDLE_LOW = 120;

/**
 * @brief A mérőjel ADC-csatornája; a beállító mód is ezt a jelutat használja.
 */
static const uint8_t CHANNEL = 0;

/**
 * @brief Bekapcsolja vagy kikapcsolja a hardveres watchdog használatát.
 *
 * A watchdog a rendszer lefagyása esetén újraindítja a kütyüt.
 */
#define USE_WATCHDOG 1

/** Ennyi inaktivitás (ms) után a kütyü alvó módba kapcsol  */
#define IDLE_SLEEP_MS (1000UL * 60UL * 5UL) // 5 perc
